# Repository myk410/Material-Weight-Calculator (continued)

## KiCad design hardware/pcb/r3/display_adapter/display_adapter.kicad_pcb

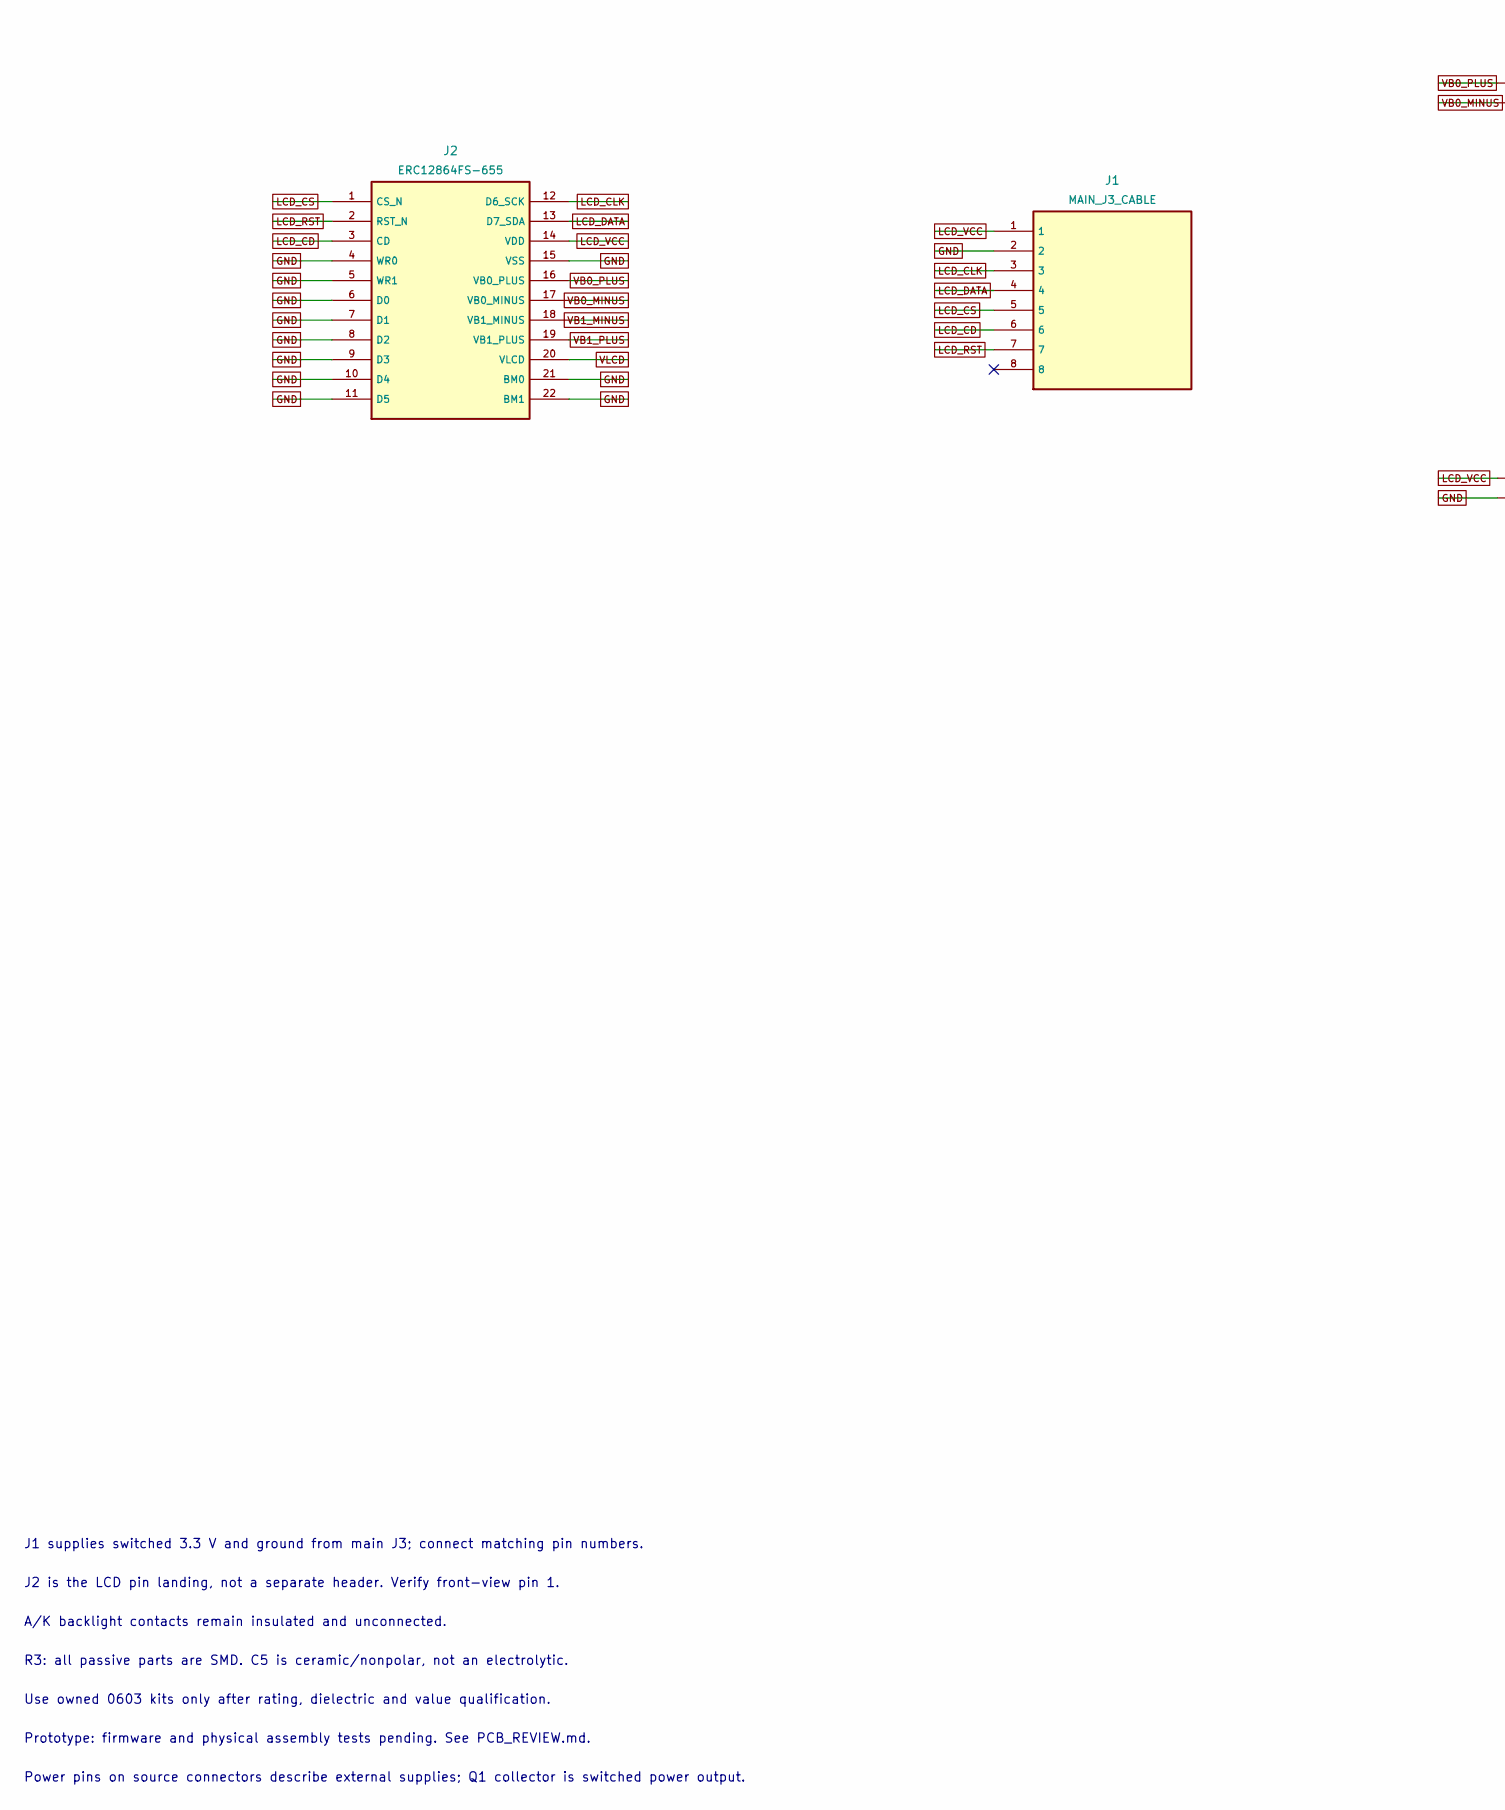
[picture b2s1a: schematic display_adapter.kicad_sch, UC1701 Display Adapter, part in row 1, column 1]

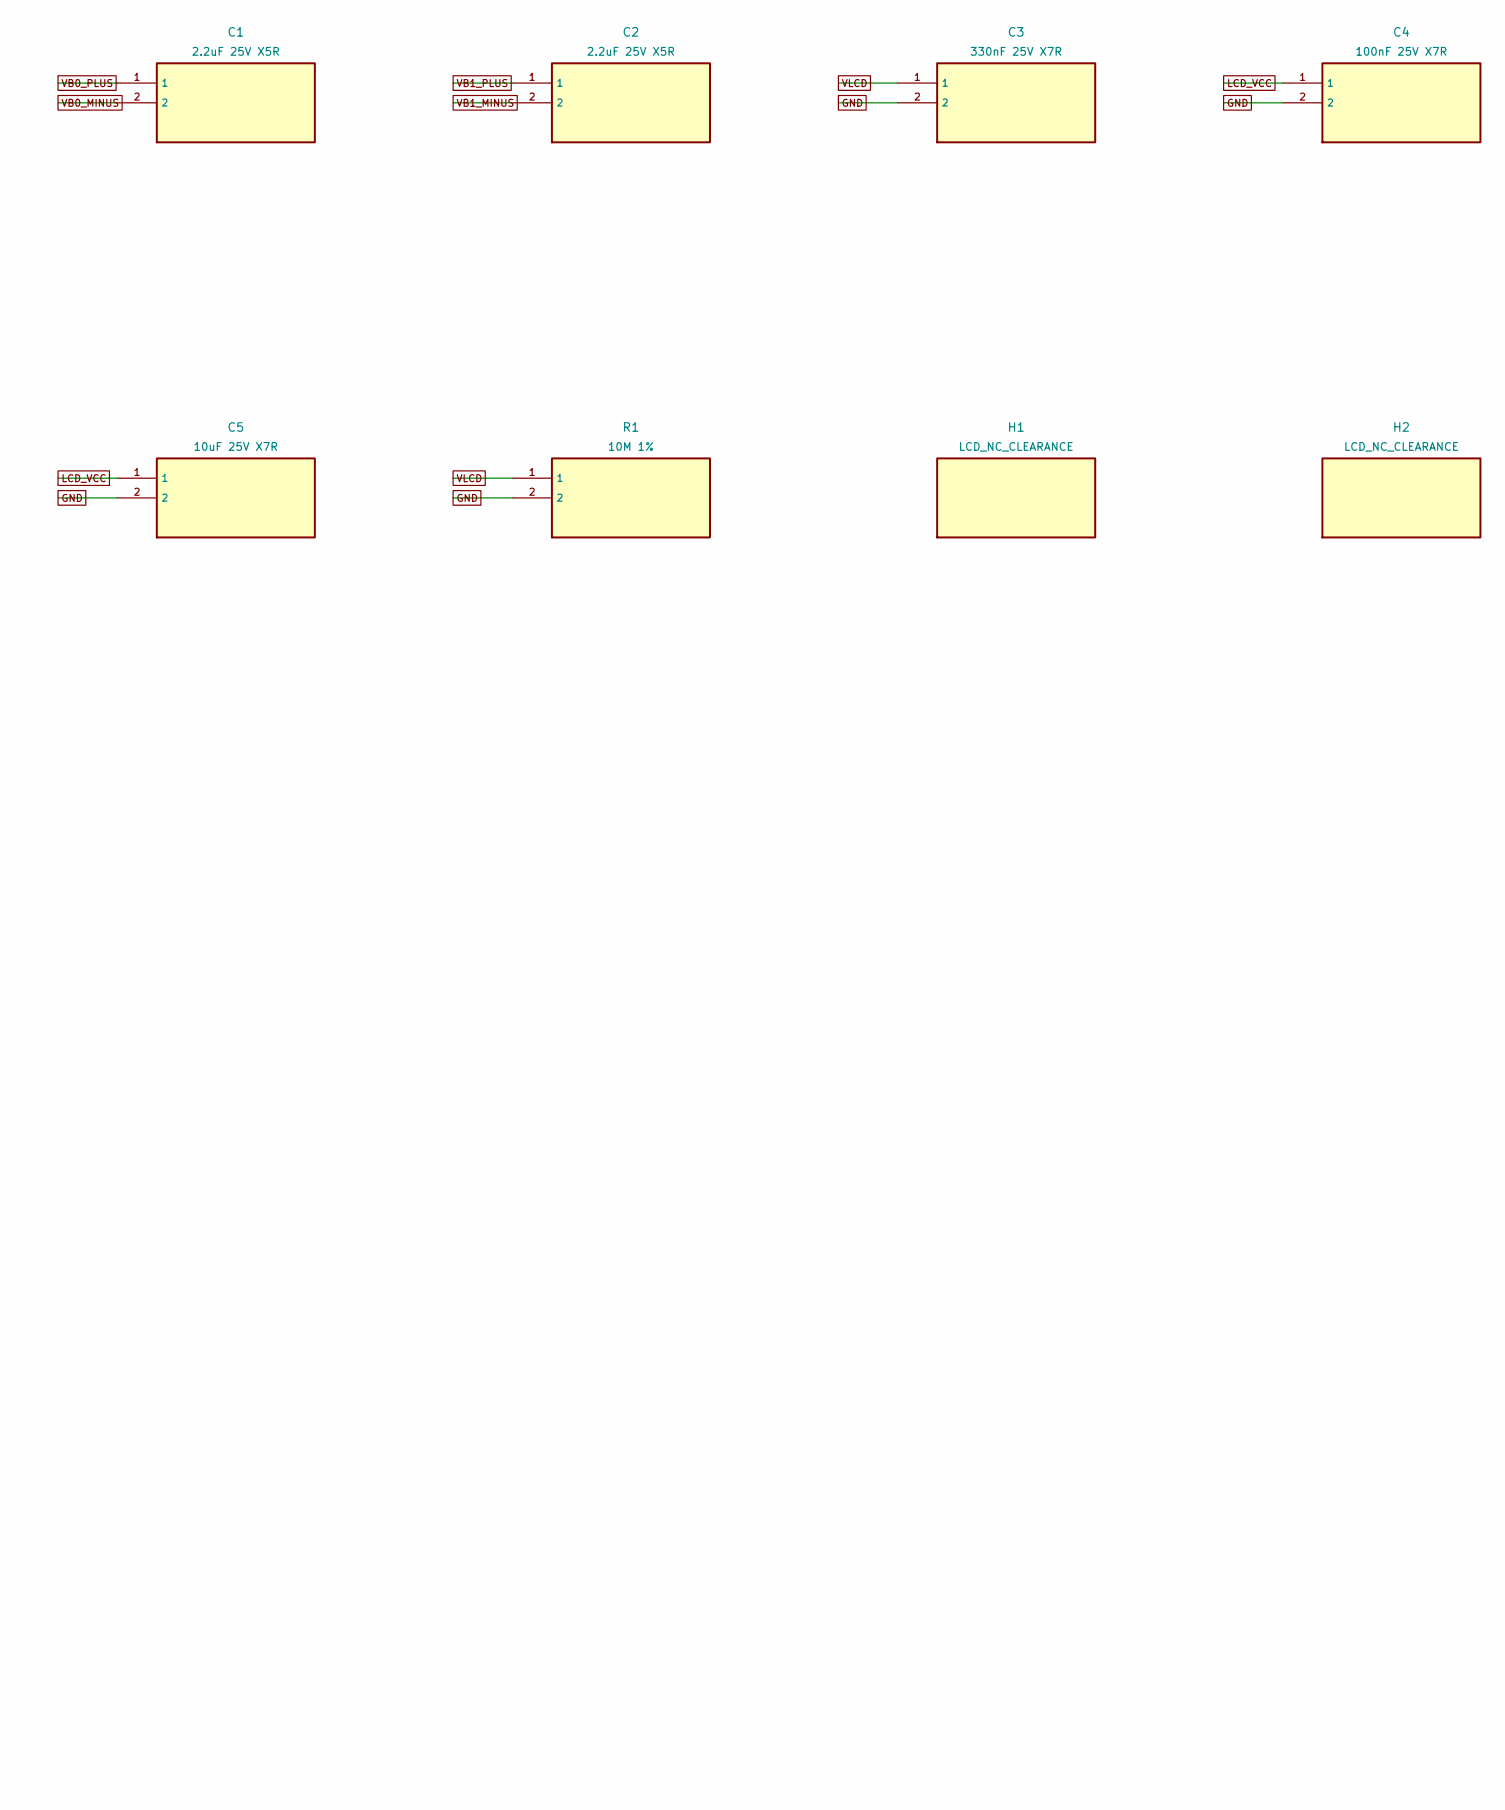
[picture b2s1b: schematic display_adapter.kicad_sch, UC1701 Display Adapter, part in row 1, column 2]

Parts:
C1, C2: 2.2uF 25V X5R; C_0603_1608Metric_Pad1.08x0.95mm_HandSolder
C3: 330nF 25V X7R; C_0603_1608Metric_Pad1.08x0.95mm_HandSolder
C4: 100nF 25V X7R; C_0603_1608Metric_Pad1.08x0.95mm_HandSolder
C5: 10uF 25V X7R; C_1206_3216Metric_Pad1.33x1.80mm_HandSolder
H1, H2: LCD_NC_CLEARANCE; MountingHole_2.1mm
J1: MAIN_J3_CABLE; PinHeader_1x08_P2.54mm_Vertical
J2: ERC12864FS-655; PinHeader_1x22_P1.27mm_Vertical
R1: 10M 1%; R_0603_1608Metric_Pad0.98x0.95mm_HandSolder

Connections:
GND: C3.2, C4.2, C5.2, J1.2, J2.4 (WR0), J2.5 (WR1), J2.6 (D0), J2.7 (D1), J2.8 (D2), J2.9 (D3), J2.10 (D4), J2.11 (D5), J2.15 (VSS), J2.21 (BM0), J2.22 (BM1), R1.2
LCD_CD: J1.6, J2.3 (CD)
LCD_CLK: J1.3, J2.12 (D6_SCK)
LCD_CS: J1.5, J2.1 (CS_N)
LCD_DATA: J1.4, J2.13 (D7_SDA)
LCD_RST: J1.7, J2.2 (RST_N)
LCD_VCC: C4.1, C5.1, J1.1, J2.14 (VDD)
VB0_MINUS: C1.2, J2.17 (VB0_MINUS)
VB0_PLUS: C1.1, J2.16 (VB0_PLUS)
VB1_MINUS: C2.2, J2.18 (VB1_MINUS)
VB1_PLUS: C2.1, J2.19 (VB1_PLUS)
VLCD: C3.1, J2.20 (VLCD), R1.1

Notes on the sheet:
J1 supplies switched 3.3 V and ground from main J3; connect matching pin numbers.
J2 is the LCD pin landing, not a separate header. Verify front-view pin 1.
A/K backlight contacts remain insulated and unconnected.
R3: all passive parts are SMD. C5 is ceramic/nonpolar, not an electrolytic.
Use owned 0603 kits only after rating, dielectric and value qualification.
Prototype: firmware and physical assembly tests pending. See PCB_REVIEW.md.
Power pins on source connectors describe external supplies; Q1 collector is switched power output.

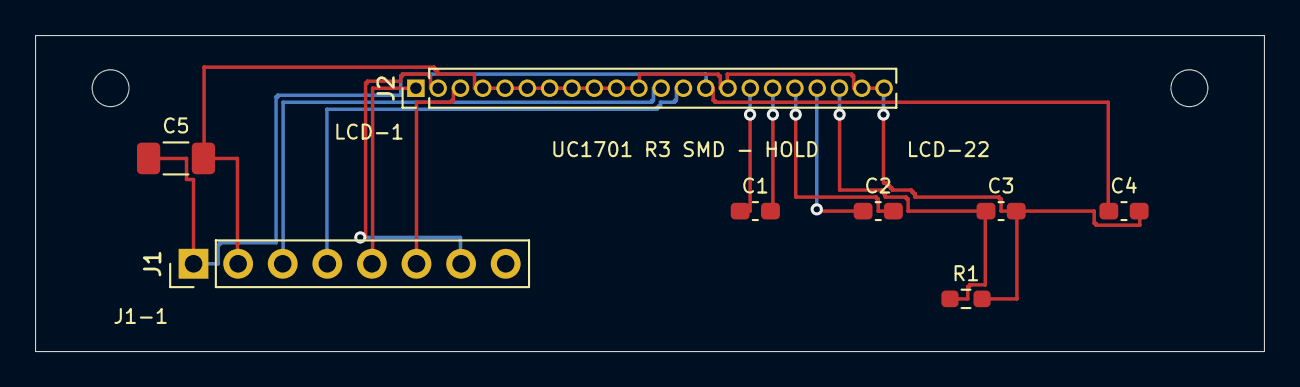
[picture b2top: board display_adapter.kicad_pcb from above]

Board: 2 copper layers, 70.0 x 18.0 mm, 10 parts (0 on the bottom side), 12 nets.

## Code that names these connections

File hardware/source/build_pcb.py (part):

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 components.append(rec);return f
# Common connector footprint orientation: pad numbers increase downward in PCB plan.
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labels=['PA7','PC0','PC1','PC2','PC3','PD0','PD1','PD2','PD3','PD4','PD5','PD6','PD7','AVDD','GND','PF0','PF1','PF6_RESET','UPDI','VDD','GND','PA0','PA1','PA2','PA3','PA4','PA5','PA6']
comp('U1','AVR128DA28-I/SP','Package_DIP','DIP-28_W7.62mm',35,20,U1,{str(i+1):s for i,s in enumerate(labels)})
comp('J1','KEYPAD_8PIN','Connector_PinHeader_2.54mm','PinHeader_1x08_P2.54mm_Vertical',12,22.54,{str(i+1):n for i,n in enumerate(['ROW0','ROW1','ROW2','ROW3','COL0','COL1','COL2','COL3'])})
comp('J2','BATTERY_3AAA','Connector_PinHeader_2.54mm','PinHeader_1x02_P2.54mm_Vertical',10,9,{'1':'BAT_PLUS','2':'GND'},{'1':'BAT+','2':'BAT-'})
comp('JP1','MASTER_LINK','Connector_PinHeader_2.54mm','PinHeader_1x02_P2.54mm_Vertical',19,9,{'1':'BAT_PLUS','2':'BAT_SWITCH'})
comp('D1','1N5817','Diode_THT','D_DO-41_SOD81_P7.62mm_Horizontal',24,9,{'1':'VIN','2':'BAT_SWITCH'},{'1':'K','2':'A'})
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comp('Q1','onsemi 2N3906 EBC','Package_TO_SOT_THT','TO-92_Inline_Wide',56,15,{'1':'+3V3','2':'LCD_BASE','3':'LCD_VCC'},{'1':'E','2':'B','3':'C'})
comp('R1','10k','Resistor_THT','R_Axial_DIN0207_L6.3mm_D2.5mm_P7.62mm_Horizontal',50,22,{'1':'LCD_PWR_CTRL','2':'LCD_BASE'})
comp('R2','100k','Resistor_THT','R_Axial_DIN0207_L6.3mm_D2.5mm_P7.62mm_Horizontal',56,7,{'1':'+3V3','2':'LCD_BASE'})
comp('J3','UC1701_ADAPTER_CABLE','Connector_PinHeader_2.54mm','PinHeader_1x08_P2.54mm_Vertical',70,16,{str(i+1):n for i,n in enumerate(['LCD_VCC','GND','LCD_CLK','LCD_DATA','LCD_CS','LCD_CD','LCD_RST',''])},{str(i+1):n for i,n in enumerate(['VCC','GND','SCK','SDA','CS_N','CD','RST_N','NC'])})
comp('J4','UPDI_3V3','Connector_PinHeader_2.54mm','PinHeader_1x03_P2.54mm_Vertical',55,46,{'1':'+3V3','2':'GND','3':'UPDI'},{'1':'VTREF','2':'GND','3':'UPDI'})
for i,(x,y) in enumerate([(5,5),(77,5),(5,63),(77,63)]):
 f=comp(f'H{i+1}','M2.5','MountingHole','MountingHole_2.7mm_M2.5',x,y,{})
# Outline.
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
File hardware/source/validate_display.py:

"""Pin audit against the EastRising module table and SPI application circuit."""
from pathlib import Path
import json,xml.etree.ElementTree as E
ROOT=Path(__file__).resolve().parents[1]
main=json.loads((ROOT/'source'/'electrical_design.json').read_text())
adapter=json.loads((ROOT/'source'/'adapter_electrical_design.json').read_text())
M={x['ref']:x for x in main['components']};A={x['ref']:x for x in adapter['components']}
assert M['J3']['pins']==A['J1']['pins']
assert M['U1']['pins']['26']=='LCD_CD' and M['U1']['pins']['27']=='LCD_RST'
expected={'1':'LCD_CS','2':'LCD_RST','3':'LCD_CD','4':'GND','5':'GND',**{str(x):'GND' for x in range(6,12)},'12':'LCD_CLK','13':'LCD_DATA','14':'LCD_VCC','15':'GND','16':'VB0_PLUS','17':'VB0_MINUS','18':'VB1_MINUS','19':'VB1_PLUS','20':'VLCD','21':'GND','22':'GND'}
assert A['J2']['pins']==expected
for ref,pair in [('C1',{'VB0_PLUS','VB0_MINUS'}),('C2',{'VB1_PLUS','VB1_MINUS'}),('C3',{'VLCD','GND'}),('R1',{'VLCD','GND'})]:assert set(A[ref]['pins'].values())==pair
assert A['C5']['pins']=={'1':'LCD_VCC','2':'GND'}
assert A['C1']['value']==A['C2']['value']=='2.2uF 50V X7R'
assert A['C3']['value']=='330nF 25V' and A['R1']['value']=='10M'
pads={p['pin']:p for p in adapter['pads'] if p['ref']=='J2'}
assert len(pads)==22 and abs(pads['22']['x']-pads['1']['x']-26.67)<1e-6
for i in range(1,22):assert abs(pads[str(i+1)]['x']-pads[str(i)]['x']-1.27)<1e-6
actual={}
for net in E.parse(ROOT/'pcb'/'display_adapter'/'display_adapter.net.xml').findall('.//nets/net'):
 if net.get('name').startswith('unconnected-'):continue
 for node in net.findall('node'):actual[(node.get('ref'),node.get('pin'))]=net.get('name').lstrip('/')
expected={(c['ref'],p):n for c in adapter['components'] for p,n in c['pins'].items() if n}
assert expected==actual
result={'display':'ERC12864FS-655','result':'PASS','matched_adapter_connected_pins':len(actual),'signal_pins':22,'pitch_mm':1.27,'cable_connected_wires':7,'backlight':'not connected','sources':['EastRising ERC12864-655 Series Rev1.0, pp7-9','EastRising SPI reference schematic dated 2020-04-21']}
(ROOT/'validation'/'display_pin_audit.json').write_text(json.dumps(result,indent=2));print(result)

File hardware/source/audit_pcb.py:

"""Check actual KiCad pad nets, copper geometry and mechanical registration.

Requires KiCad 9 pcbnew. The source JSON is checked against the saved board;
critical device connections below are also checked against explicit datasheet
pin assignments rather than inferred from the board generator's labels.
"""
from collections import Counter
from pathlib import Path
import ast
import json
import xml.etree.ElementTree as E
import pcbnew as k

ROOT = Path(__file__).resolve().parents[1]


def point(v):
    return (round(v.x / 1e6 - 50, 4), round(v.y / 1e6 - 50, 4))


def run():
    reports, boards, definitions = {}, {}, {}
    for adapter in (False, True):
        name = 'adapter' if adapter else 'main'
        folder = ROOT / 'pcb' / 'display_adapter' if adapter else ROOT / 'pcb'
        stem = 'display_adapter' if adapter else 'material_weight_calculator'
        data = json.loads((ROOT / 'source' / ('adapter_electrical_design.json' if adapter else 'electrical_design.json')).read_text())
        board = k.LoadBoard(str(folder / (stem + '.kicad_pcb')))
        boards[name] = board
        definitions[name] = {c['ref']: c for c in data['components']}
        expected = {(c['ref'], p): n for c in data['components'] for p, n in c['pins'].items() if n}
        actual = {}
        pads = {(p['ref'], p['pin']): p for p in data['pads']}
        for fp in board.GetFootprints():
            c = definitions[name][fp.GetReference()]
            assert point(fp.GetPosition()) == (round(c['x'],4), round(c['y'],4)), (name, c['ref'], point(fp.GetPosition()), (c['x'],c['y']))
            assert fp.GetFPIDAsString() == c['footprint']
            for pad in fp.Pads():
                key = (fp.GetReference(), pad.GetNumber())
                assert point(pad.GetPosition()) == (round(pads[key]['x'], 4), round(pads[key]['y'], 4)), key
                assert abs(pad.GetDrillSize().x / 1e6 - pads[key]['drill']) < 1e-6
                n = pad.GetNetname()
                if n and not n.startswith('unconnected-'): actual[key] = n
        assert expected == actual, name
        schema = {}
        for net in E.parse(folder / (stem + '.net.xml')).findall('.//nets/net'):
            n = net.get('name')
            if n.startswith('unconnected-'): continue
            for node in net.findall('node'):
                if not node.get('ref').startswith('#'):
                    schema[node.get('ref'), node.get('pin')] = n
        assert schema == actual, name

        def seg(n, layer, a, b, width):
            return (n, layer, tuple(sorted((tuple(round(v, 4) for v in a), tuple(round(v, 4) for v in b)))), round(width, 6))
        tracks = Counter(); vias = Counter()
        for track in board.GetTracks():
            if isinstance(track, k.PCB_VIA):
                vias[(track.GetNetname(), point(track.GetPosition()), track.GetWidth(k.F_Cu)/1e6, track.GetDrillValue()/1e6)] += 1
            else:
                layer = 0 if track.GetLayer() == k.F_Cu else 1
                tracks[seg(track.GetNetname(), layer, point(track.GetStart()), point(track.GetEnd()), track.GetWidth()/1e6)] += 1
        assert tracks == Counter(seg(t['net'], t['layer'], t['a'], t['b'], t['width']) for t in data['routes']), name
        assert vias == Counter((v['net'], (round(v['x'],4),round(v['y'],4)), 1.0, .5) for v in data['vias']), name
        box = board.GetBoardEdgesBoundingBox()
        # Edge bounding box includes half the 0.05 mm outline stroke on each side.
        size = [round(box.GetWidth()/1e6 - .05, 3), round(box.GetHeight()/1e6 - .05, 3)]
        assert size == data['board_size_mm'], size
        reports[name] = {'result': 'PASS', 'connected_pins': len(actual), 'track_segments': sum(tracks.values()),
                         'vias': sum(vias.values()), 'size_mm': size, 'pad_positions_drills_and_copper_match_source': True}

    m, a = definitions['main'], definitions['adapter']
    # Microchip DS40002183E, 28-pin SPDIP; DS20001826F, TO-92;
    # onsemi 2N3906/D; EastRising ERC12864-655 Rev1.0 pp7-9.
    assert {p:m['U1']['pins'][p] for p in ['14','15','19','20','21','23','24','25','26','27','13']} == {
        '14':'+3V3','15':'GND','19':'UPDI','20':'+3V3','21':'GND','23':'LCD_CLK','24':'LCD_DATA','25':'LCD_CS','26':'LCD_CD','27':'LCD_RST','13':'LCD_PWR_CTRL'}
    assert m['U2']['pins'] == {'1':'GND','2':'VIN','3':'+3V3'}
    assert m['D1']['pins'] == {'1':'VIN','2':'VBAT_LINK'}  # cathode, anode
    assert m['Q1']['pins'] == {'1':'+3V3','2':'LCD_BASE','3':'LCD_VCC'}  # E B C
    assert m['J2']['pins'] == {'1':'VBAT_SW','2':'GND'}
    assert m['JP1']['pins'] == {'1':'VBAT_SW','2':'VBAT_LINK'}
    assert m['J3']['pins'] == a['J1']['pins']
    assert m['J4']['pins'] == {'1':'+3V3','2':'GND','3':'UPDI'}
    # Main mounting positions must register with the case's actual source, not
    # just its board proxy. Parse the literal list without executing CAD exports.
    tree = ast.parse((ROOT/'source'/'build_case.py').read_text())
    holes = next(ast.literal_eval(n.value) for n in tree.body if isinstance(n, ast.Assign) and any(isinstance(t,ast.Name) and t.id=='pcbholes' for t in n.targets))
    params = json.loads((ROOT/'source'/'mechanical_parameters.json').read_text())
    origin = params['pcb_origin_plan_mm']
    mounted = [(m['H'+str(i)]['x']+origin[0], m['H'+str(i)]['y']+origin[1]) for i in range(1,5)]
    assert mounted == holes
    for board_name, refs in [('main', ['C1','C2','C5']),('adapter',['C1','C2'])]:
        for ref in refs:
            c=definitions[board_name][ref]
            assert c['value']=='2.2uF 50V X7R' and c['manufacturer_part_number']=='FG14X7R1H225KRT00'
    # Nominal installed height of the selected flying caps, not a full CAD fit test.
    assert 13 + 1.6 + 5.5 + .5 <= 22.1
    result={'revision':'R2.1','result':'PASS','boards':reports,'critical_pin_maps':'PASS',
            'main_holes_match_case_source':True,'selected_adapter_capacitor_height_clearance_mm':2.0,
            'limits':['No bench measurements or physical assembly test.',
                      'Generic remaining passive footprints still require selected-part body/lead checks.',
                      'Nominal capacitor height arithmetic is not a populated-component CAD collision test.']}
    (ROOT/'validation'/'pcb_audit.json').write_text(json.dumps(result,indent=2)+'\n')
    print(json.dumps(result, indent=2))


if __name__ == '__main__': run()
